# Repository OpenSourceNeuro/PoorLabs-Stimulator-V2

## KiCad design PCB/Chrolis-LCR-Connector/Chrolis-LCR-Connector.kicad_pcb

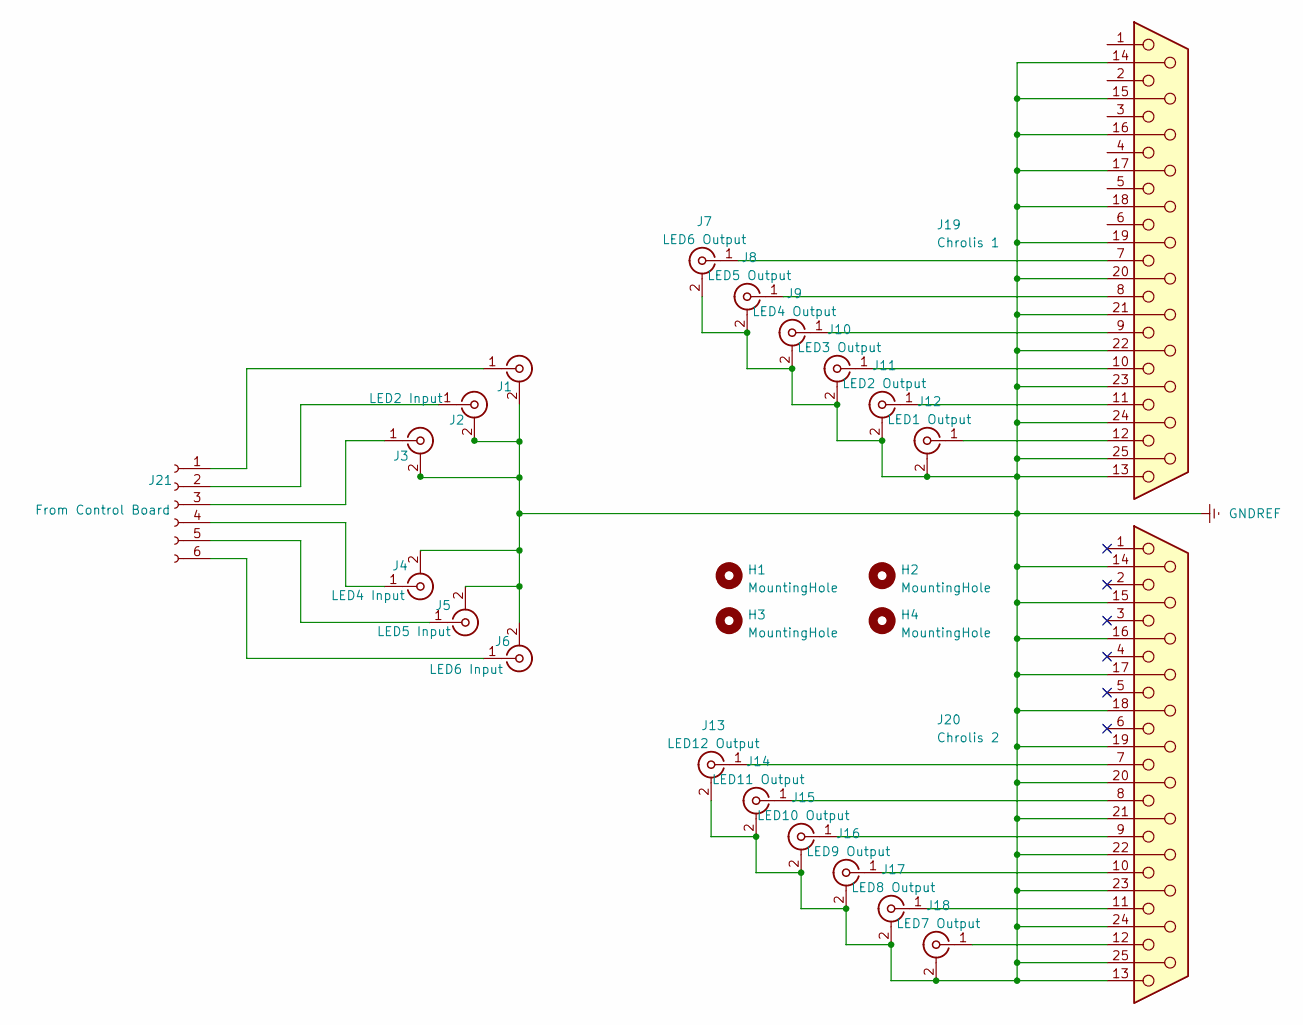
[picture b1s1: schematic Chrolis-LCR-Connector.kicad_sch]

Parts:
H1, H2, H3, H4: MountingHole; MountingHole_3mm
J1, J3: (no value)
J2: LED2 Input; SMA_Amphenol_132291_Vertical
J4: LED4 Input; SMA_Amphenol_132291_Vertical
J5: LED5 Input; SMA_Amphenol_132291_Vertical
J6: LED6 Input; SMA_Amphenol_132291_Vertical
J7: LED6 Output; SMA_Amphenol_132291_Vertical
J8: LED5 Output; SMA_Amphenol_132291_Vertical
J9: LED4 Output; SMA_Amphenol_132291_Vertical
J10: LED3 Output; SMA_Amphenol_132291_Vertical
J11: LED2 Output; SMA_Amphenol_132291_Vertical
J12: LED1 Output; SMA_Amphenol_132291_Vertical
J13: LED12 Output; SMA_Amphenol_132291_Vertical
J14: LED11 Output; SMA_Amphenol_132291_Vertical
J15: LED10 Output; SMA_Amphenol_132291_Vertical
J16: LED9 Output; SMA_Amphenol_132291_Vertical
J17: LED8 Output; SMA_Amphenol_132291_Vertical
J18: LED7 Output; SMA_Amphenol_132291_Vertical
J19: Chrolis 1; DSUB-25_Female_Horizontal_P2.77x2.84mm_EdgePinOffset9.90mm_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
J20: Chrolis 2; DSUB-25_Female_Horizontal_P2.77x2.84mm_EdgePinOffset9.90mm_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
J21: From Control Board; JST_XH_S6B-XH-A_1x06_P2.50mm_Horizontal

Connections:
GNDREF: J1.2 (Ext), J4.2 (Ext), J5.2 (Ext), J6.2 (Ext), J7.2 (Ext), J8.2 (Ext), J9.2 (Ext), J10.2 (Ext), J11.2 (Ext), J12.2 (Ext), J13.2 (Ext), J14.2 (Ext), J15.2 (Ext), J16.2 (Ext), J17.2 (Ext), J18.2 (Ext), J19.13, J19.14, J19.15, J19.16, J19.17, J19.18, J19.19, J19.20, J19.21, J19.22, J19.23, J19.24, J19.25, J20.13, J20.14, J20.15, J20.16, J20.17, J20.18, J20.19, J20.20, J20.21, J20.22, J20.23, J20.24, J20.25
unnamed: J1.1 (In), J21.1
unnamed: J2.1 (In), J21.2
unnamed: J10.1 (In), J19.10
unnamed: J11.1 (In), J19.11
unnamed: J12.1 (In), J19.12
unnamed: J13.1 (In), J20.7
unnamed: J14.1 (In), J20.8
unnamed: J15.1 (In), J20.9
unnamed: J16.1 (In), J20.10
unnamed: J17.1 (In), J20.11
unnamed: J18.1 (In), J20.12
unnamed: J7.1 (In), J19.7
unnamed: J8.1 (In), J19.8
unnamed: J9.1 (In), J19.9
unnamed: J3.1 (In), J21.3
unnamed: J4.1 (In), J21.4
unnamed: J5.1 (In), J21.5
unnamed: J6.1 (In), J21.6

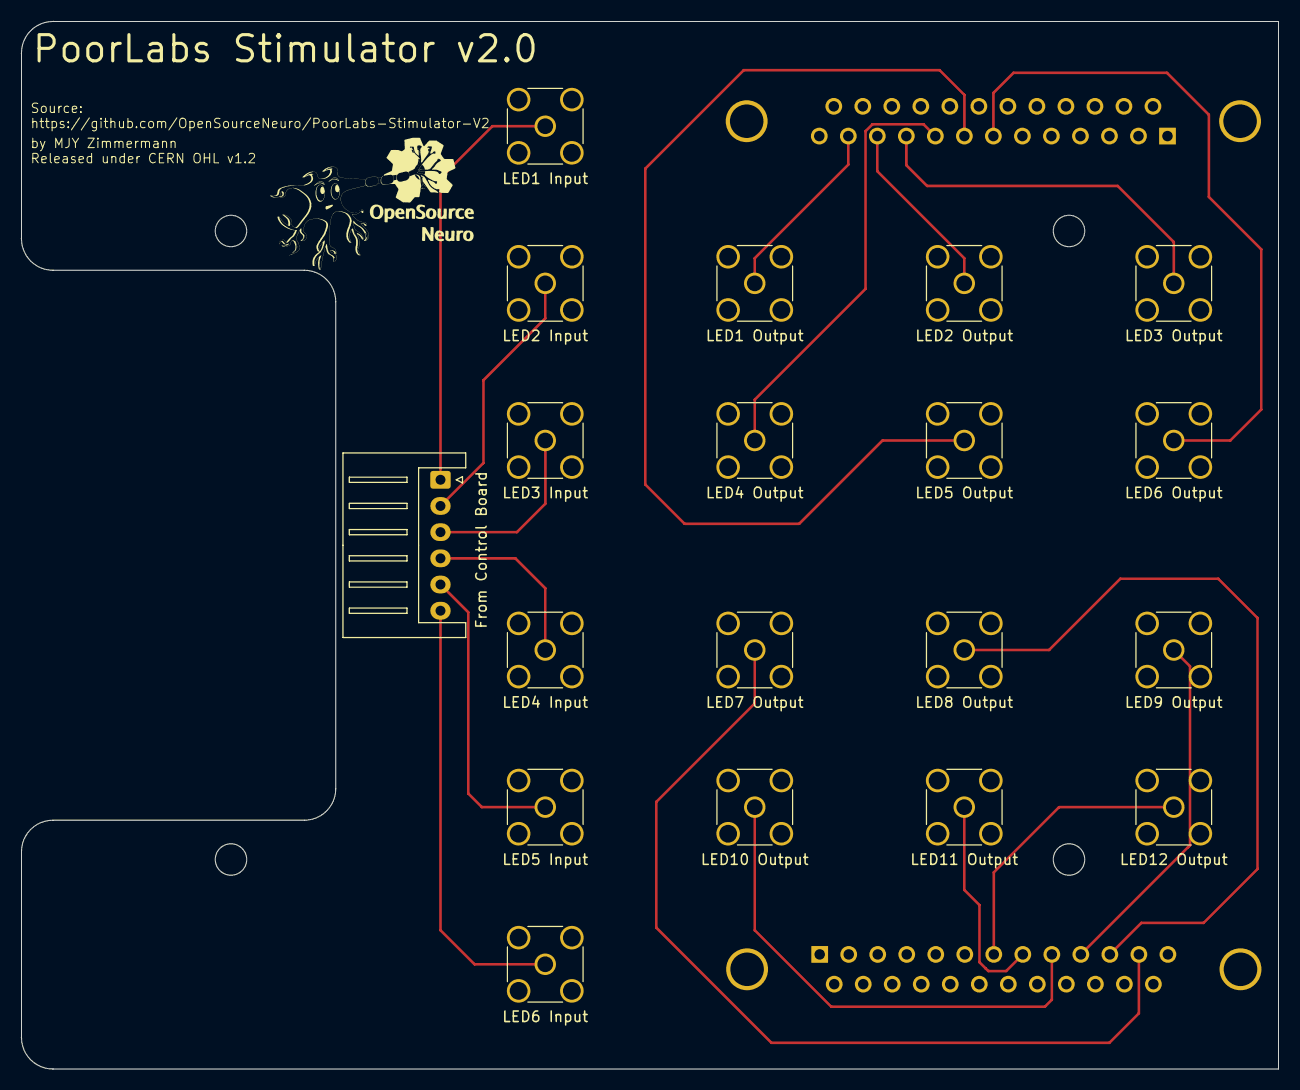
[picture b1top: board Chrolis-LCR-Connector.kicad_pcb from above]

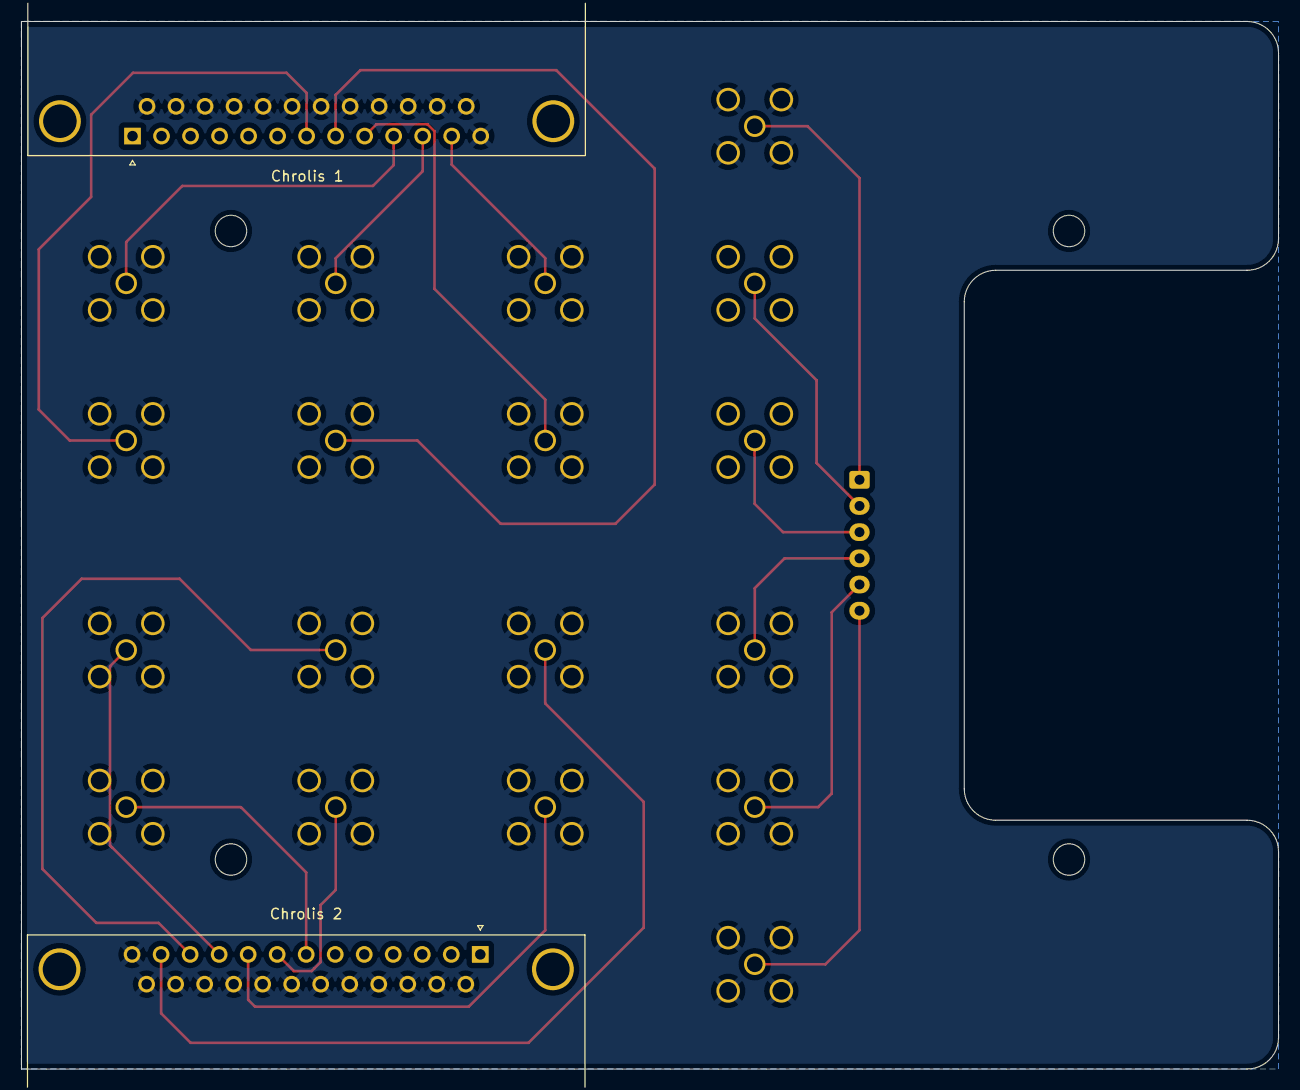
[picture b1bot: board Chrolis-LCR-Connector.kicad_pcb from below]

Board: 2 copper layers, 120.0 x 100.0 mm, 25 parts (2 on the bottom side), 19 nets.

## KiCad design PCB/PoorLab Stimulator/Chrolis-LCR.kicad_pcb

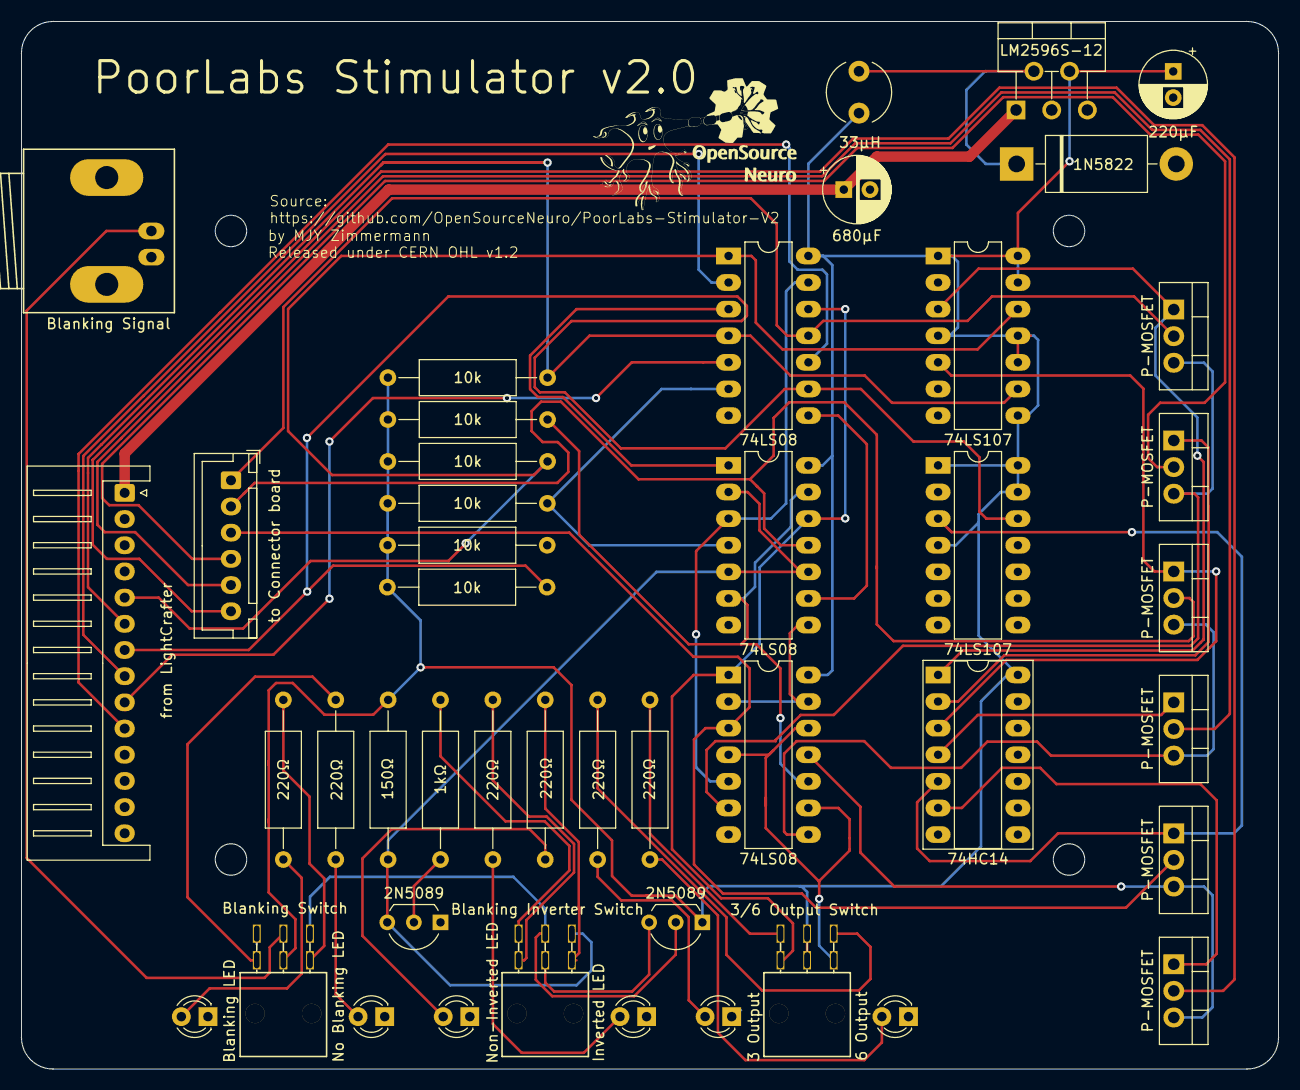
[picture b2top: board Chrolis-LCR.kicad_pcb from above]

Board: 2 copper layers, 120.0 x 100.0 mm, 49 parts (0 on the bottom side), 51 nets.

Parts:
C1: 220μF; CP_Radial_D6.3mm_P2.50mm
C2: 680μF; CP_Radial_D6.3mm_P2.50mm
D1: Blanking LED; LED_D3.0mm
D2: No Blanking LED; LED_D3.0mm
D3: Inverted LED; LED_D3.0mm
D4: Non-Inverted LED; LED_D3.0mm
D5: 3 Output; LED_D3.0mm
D6: 6 Output; LED_D3.0mm
D7: 1N5822; D_DO-201AD_P15.24mm_Horizontal
H1, H2, H3, H4: MountingHole; MountingHole_3mm
J1: Blanking Signal; BNC_Socket_TYCO-AMP_LargePads
J2: from LightCrafter; JST_XH_S14B-XH-A_1x14_P2.50mm_Horizontal
J3: to Connector board; JST_XH_B6B-XH-A_1x06_P2.50mm_Vertical
L1: 33μH; L_Radial_D6.0mm_P4.00mm
Q0, Q1: 2N5089; TO-92L_Inline_Wide
Q2, Q3, Q4, Q5, Q6, Q7: P-MOSFET; TO-220-3_Vertical
R1, R2, R5, R6, R7, R8: 220Ω; R_Axial_DIN0309_L9.0mm_D3.2mm_P15.24mm_Horizontal
R3: 150Ω; R_Axial_DIN0309_L9.0mm_D3.2mm_P15.24mm_Horizontal
R4: 1kΩ; R_Axial_DIN0309_L9.0mm_D3.2mm_P15.24mm_Horizontal
R9, R10, R12, R13, R15, R16: 10k; R_Axial_DIN0309_L9.0mm_D3.2mm_P15.24mm_Horizontal
SW1: Blanking Switch; maxi_DPDT_Angled
SW2: Blanking Inverter Switch; maxi_DPDT_Angled
SW3: 3/6 Output Switch; maxi_DPDT_Angled
U0: LM2596S-12; TO-220-5_P3.4x3.7mm_StaggerOdd_Lead3.8mm_Vertical
U1, U2, U3: 74LS08; DIP-14_W7.62mm_LongPads
U4: 74HC14; DIP-14_W7.62mm_Socket_LongPads
U5, U6: 74LS107; DIP-14_W7.62mm_LongPads

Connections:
3LED switch: SW3.4 (A), U1.12, U2.12, U3.1
5V: C1.1, L1.2, Q0.1 (E), R3.2, R9.1, R10.2, R12.1, R13.1, R15.1, R16.1, SW1.5 (B), SW3.2 (B), SW3.5 (B), U0.4 (FB), U1.14 (VCC), U2.14 (VCC), U3.14 (VCC), U4.14 (VCC), U5.1 (J), U5.4 (K), U5.8 (J), U5.10 (~R), U5.11 (K), U5.13 (~R), U5.14 (VCC), U6.1 (J), U6.4 (K), U6.13 (~R), U6.14 (VCC)
6LED switch: SW3.6 (C), U3.4, U3.9, U3.12
6LED/LED1 Input: Q2.3 (S), Q3.3 (S), U3.6
6LED/LED2 Input: Q4.3 (S), Q5.3 (S), U3.8
6LED/LED3 Input: Q6.3 (S), Q7.3 (S), U3.11
12V: C2.1, J2.1, U0.1 (VIN)
Blanking: Q1.3 (C), R3.1, SW2.3 (C), U2.2, U2.5, U2.10
GNDREF: C1.2, C2.2, D1.1 (K), D2.1 (K), D3.1 (K), D4.1 (K), D5.1 (K), D6.1 (K), D7.2 (A), J1.2 (Ext), J2.12, J2.13, J2.14, Q1.1 (E), U0.3 (GND), U0.5 (~ON/OFF), U1.7 (GND), U2.7 (GND), U3.7 (GND), U4.7 (GND), U5.7 (GND), U6.7 (GND)
LED1 Input: J3.1, Q2.2 (D), U1.11
LED1 PWM: J2.8, U1.2
LED1 blanked: U1.13, U2.3, U3.5
LED1 enable: J2.5, R9.2, U1.1, U5.12 (C)
LED2 Input: J3.2, Q4.2 (D), U2.11
LED2 PWM: J2.9, U1.5
LED2 blanked: U2.6, U2.13, U3.10
LED2 enable: J2.6, R12.2, U1.4, U5.9 (C)
LED3 Input: J3.3, Q6.2 (D), U3.3
LED3 PWM: J2.10, U1.10
LED3 blanked: U2.8, U3.2, U3.13
LED3 enable: J2.7, R15.2, U1.9, U6.12 (C)
LED4 Input: J3.4, Q3.2 (D)
LED5 Input: J3.5, Q5.2 (D)
LED6 Input: J3.6, Q7.2 (D)
Latch LED1: Q2.1 (G), U4.1, U5.3 (Q)
Latch LED2: Q4.1 (G), U4.3, U5.5 (Q)
Latch LED3: Q6.1 (G), U4.5, U6.3 (Q)
unnamed: D1.2 (A), R1.1
unnamed: D2.2 (A), R2.1
unnamed: D3.2 (A), R5.1
unnamed: D4.2 (A), R6.1
unnamed: D5.2 (A), R7.1
unnamed: D6.2 (A), R8.1
unnamed: D7.1 (K), L1.1, U0.2 (OUT)
unnamed: J1.1 (In), SW1.2 (B)
unnamed: Q0.2 (B), SW1.3 (C), SW2.2 (B)
unnamed: Q0.3 (C), SW2.5 (B)
unnamed: Q1.2 (B), R4.1
unnamed: Q3.1 (G), U4.2
unnamed: Q5.1 (G), U4.4
unnamed: Q7.1 (G), U4.6
unnamed: R1.2, SW1.6 (C)
unnamed: R2.2, SW1.4 (A)
unnamed: R4.2, SW2.1 (A)
unnamed: R5.2, SW2.4 (A)
unnamed: R6.2, SW2.6 (C)
unnamed: R7.2, SW3.3 (C)
unnamed: R8.2, SW3.1 (A)
unnamed: U1.3, U2.1
unnamed: R10.1, U1.6, U2.4
unnamed: U1.8, U2.9

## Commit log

2023-07-23 First Commit 3D
2023-07-23 First commit Documentation
2023-07-23 First commit PCB

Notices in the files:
PCB/Chrolis-LCR-Connector/Chrolis-LCR-Connector.kicad_pcb:
Released under CERN OHL v1.2
